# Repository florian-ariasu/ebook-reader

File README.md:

# OpenBook E-Reader

A portable, open-source e-book reader built around the **ESP32-C6** microcontroller, featuring an energy-efficient E-Paper display, microSD storage, environmental sensing, and a comprehensive power management system.

---

## System Architecture

### Block Diagram

The architecture focuses on a high-efficiency 3.3V power rail and shared communication buses (SPI/I2C):

- **ESP32-C6** – Main MCU managing UI, file systems, and wireless connectivity.
- **E-Paper Display** – 1.5" (200x200px) ultra-low-power screen.
- **Power Management** – Includes the **XC6220** 1A LDO for 3.3V regulation and **MCP73831** for Li-Po charging.
- **Battery Monitoring** – **MAX17048G+T10** fuel gauge for precision voltage and SoC tracking.
- **RTC (DS3231SN)** – Real-time clock with a **CPH3225A Supercapacitor** for power backup.
- **BME680 Sensor** – Integrated environmental sensing (Temp, Humidity, Pressure, Gas).
- **External Flash (64MB)** – Winbond **W25Q512** for extended storage and caching.

---

## Bill of Materials (BOM)

Access the full list of components used in this design, including technical specifications and sourcing links:

[Access the Bill of Materials (CSV)](Manufacturing/BOM.csv)

---

## Hardware Overview

### Power Supply & Charging

The system supports primary power via **USB-C** (5V). Charging is handled by the **MCP73831** controller. A high-performance **XC6220A331MR-G** LDO regulator converts the input/battery voltage to a stable **3.3V** to power the ESP32 and peripherals. Circuit protection includes a **USBLC6-2SC6Y** ESD protector and several **PGB1010** varistors.

### Storage Subsystems

- **MicroSD Card (J4)**: SPI-based interface for external library storage
- **NOR Flash (U1)**: 512Mb (64MB) SPI flash memory for firmware extensions

---

## ESP32-C6 Pin Allocation

| Function           | ESP32-C6 Pins        | Notes                       |
|--------------------|----------------------|-----------------------------|
| MicroSD Card       | IO2, IO3, IO4, IO5   | SPI                         |
| E-Paper Display    | IO8, IO9, IO10       | SPI                         |
| Shared I2C Bus     | IO6 (SCL), IO7 (SDA) | BME680, RTC, and Fuel Gauge |
| External Flash     | IO0, IO1, IO2        | SPI (Shared Bus)            |
| Reset Button       | IO9                  | Reset functionality         |
| UI Button (Change) | IO10                 | Navigation/Mode control     |
| UART Debug         | IO20 (TX), IO21 (RX) | Serial communication        |

---

## Visual Assets

All design-related documentation is located in the `Images/` directory:

- [Schematic](Images/schematic.png)
- [PCB Top View](Images/pcb-top.png)
- [PCB Bottom View](Images/pcb-bottom.png)
- [3D Model](Images/3d-model-2.png)
- [OpenBook Enclosure](Images/3d-model-enclosure.png)

---

## Known Issues

- **SMD Hole Errors**: Two minor SMD hole warnings were manually approved during the PCB routing phase. These were verified as non-critical for the final manufacturing.

---

## Compliance & Design Constraints

- All SMD components are **0402** package size (unless specified).
- Optimized for single-side component placement (Top-layer).
- Implemented via stitching and dual-layer ground planes for thermal/EMC stability.
- RF Isolation: The ESP32 antenna area is kept clear of copper and traces.
- Passed all Design Rule Checks (DRC) and Electrical Rule Checks (ERC).

---

- Designed the full ESP32-C6 pinout across SPI and I²C buses, integrating the E-Paper display, BME680 sensor, RTC, fuel gauge, NOR flash, and microSD card on shared communication lines.
- Managed the PCB routing phase in Autodesk Fusion 360, resolving DRC and ERC violations and manually approving non-critical SMD hole warnings after physical verification.
- Implemented dual-layer ground planes with via stitching for thermal and EMC stability, and maintained RF isolation by keeping the ESP32 antenna area clear of copper and traces.

---

## Development Notes

This is a 3rd-year TSC course assignment, designed in Autodesk Fusion 360 using a student license.

---

## Licensing

This project is licensed under the **[GPL-3.0 license](LICENCE)**.

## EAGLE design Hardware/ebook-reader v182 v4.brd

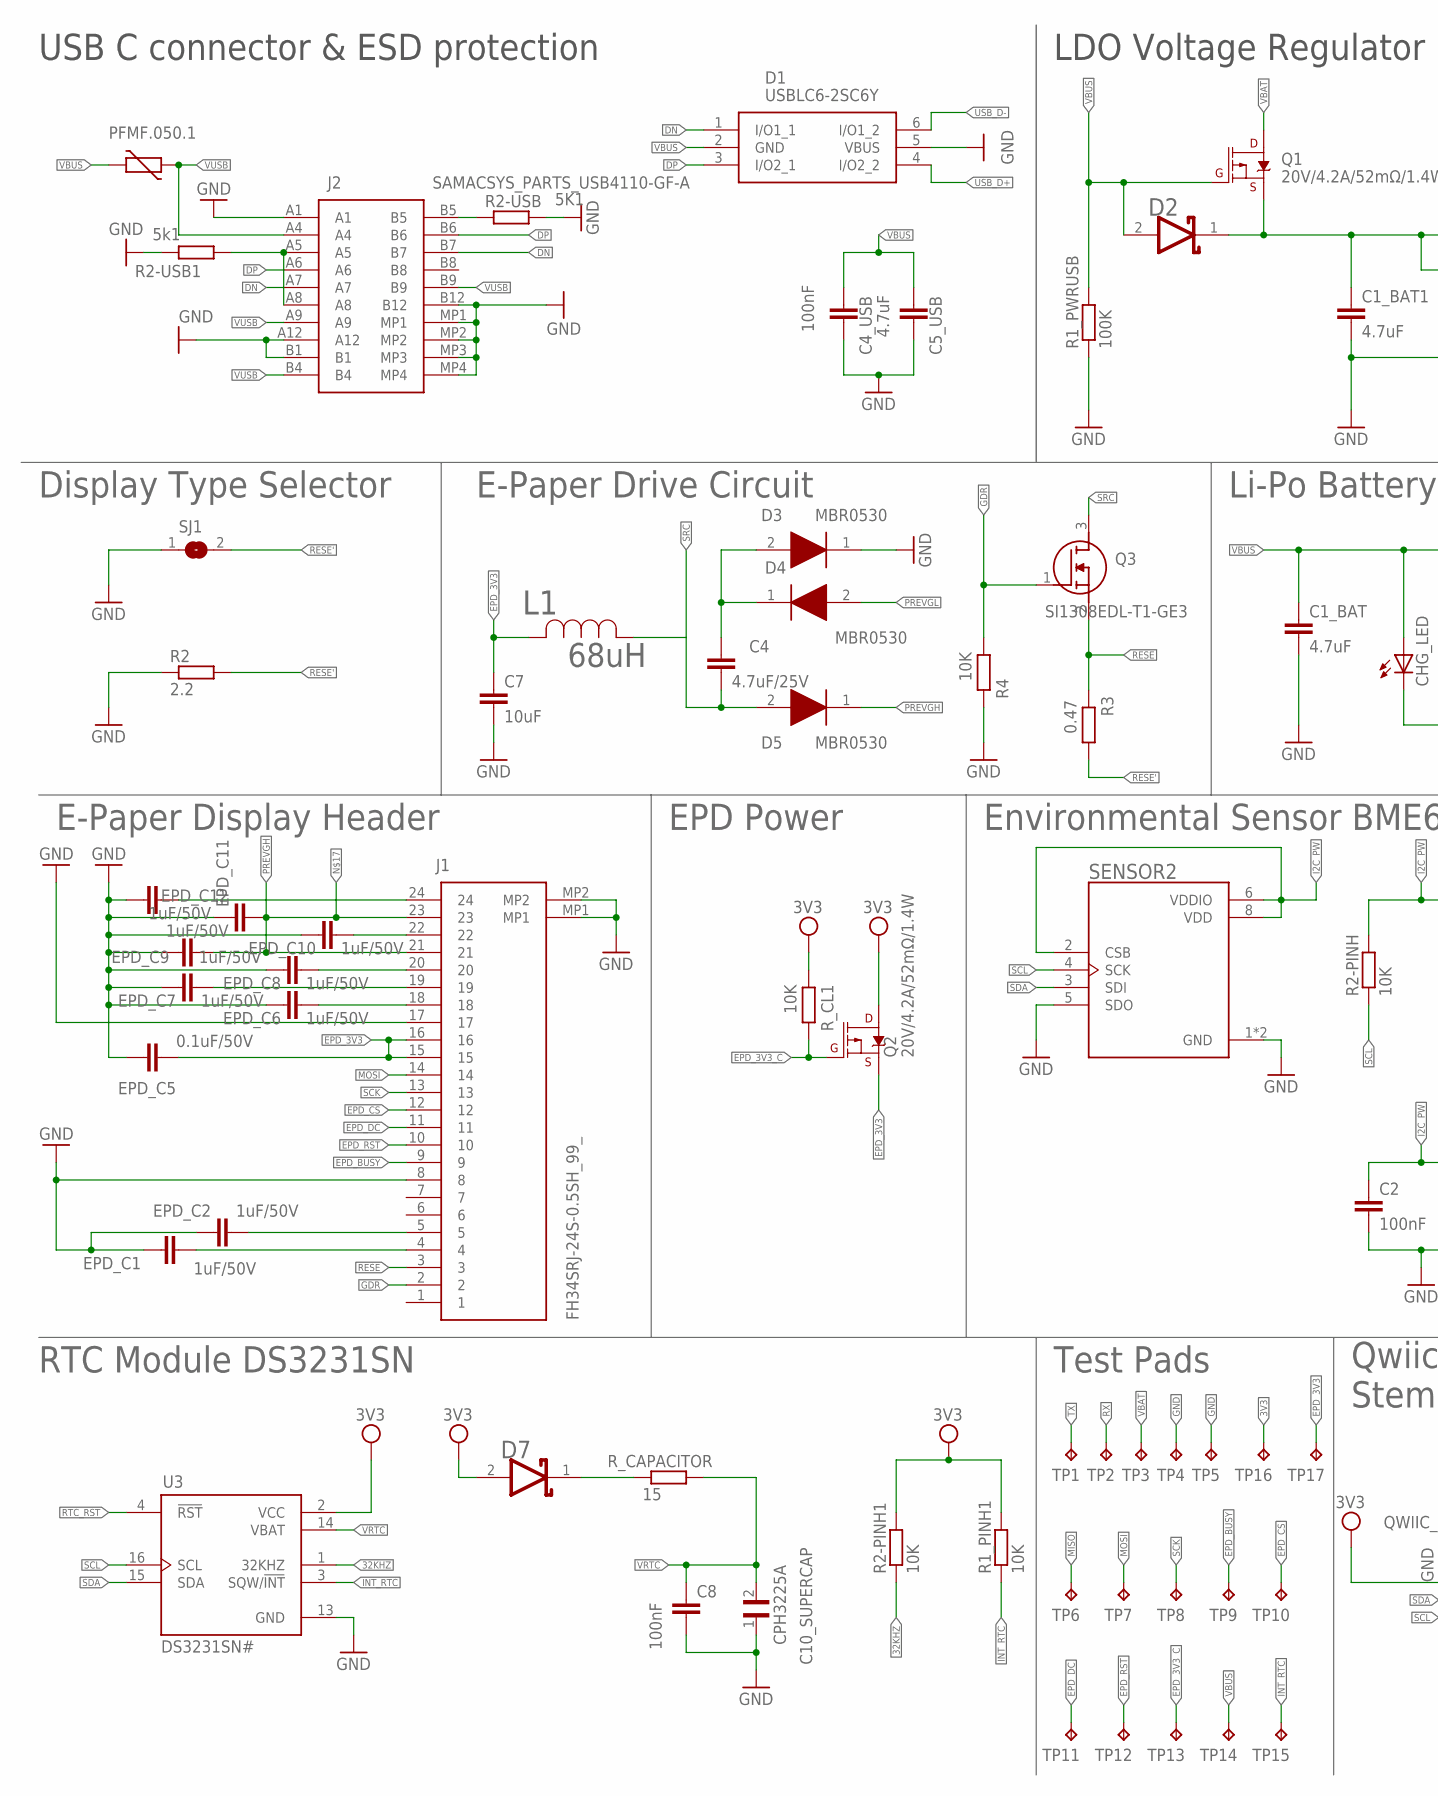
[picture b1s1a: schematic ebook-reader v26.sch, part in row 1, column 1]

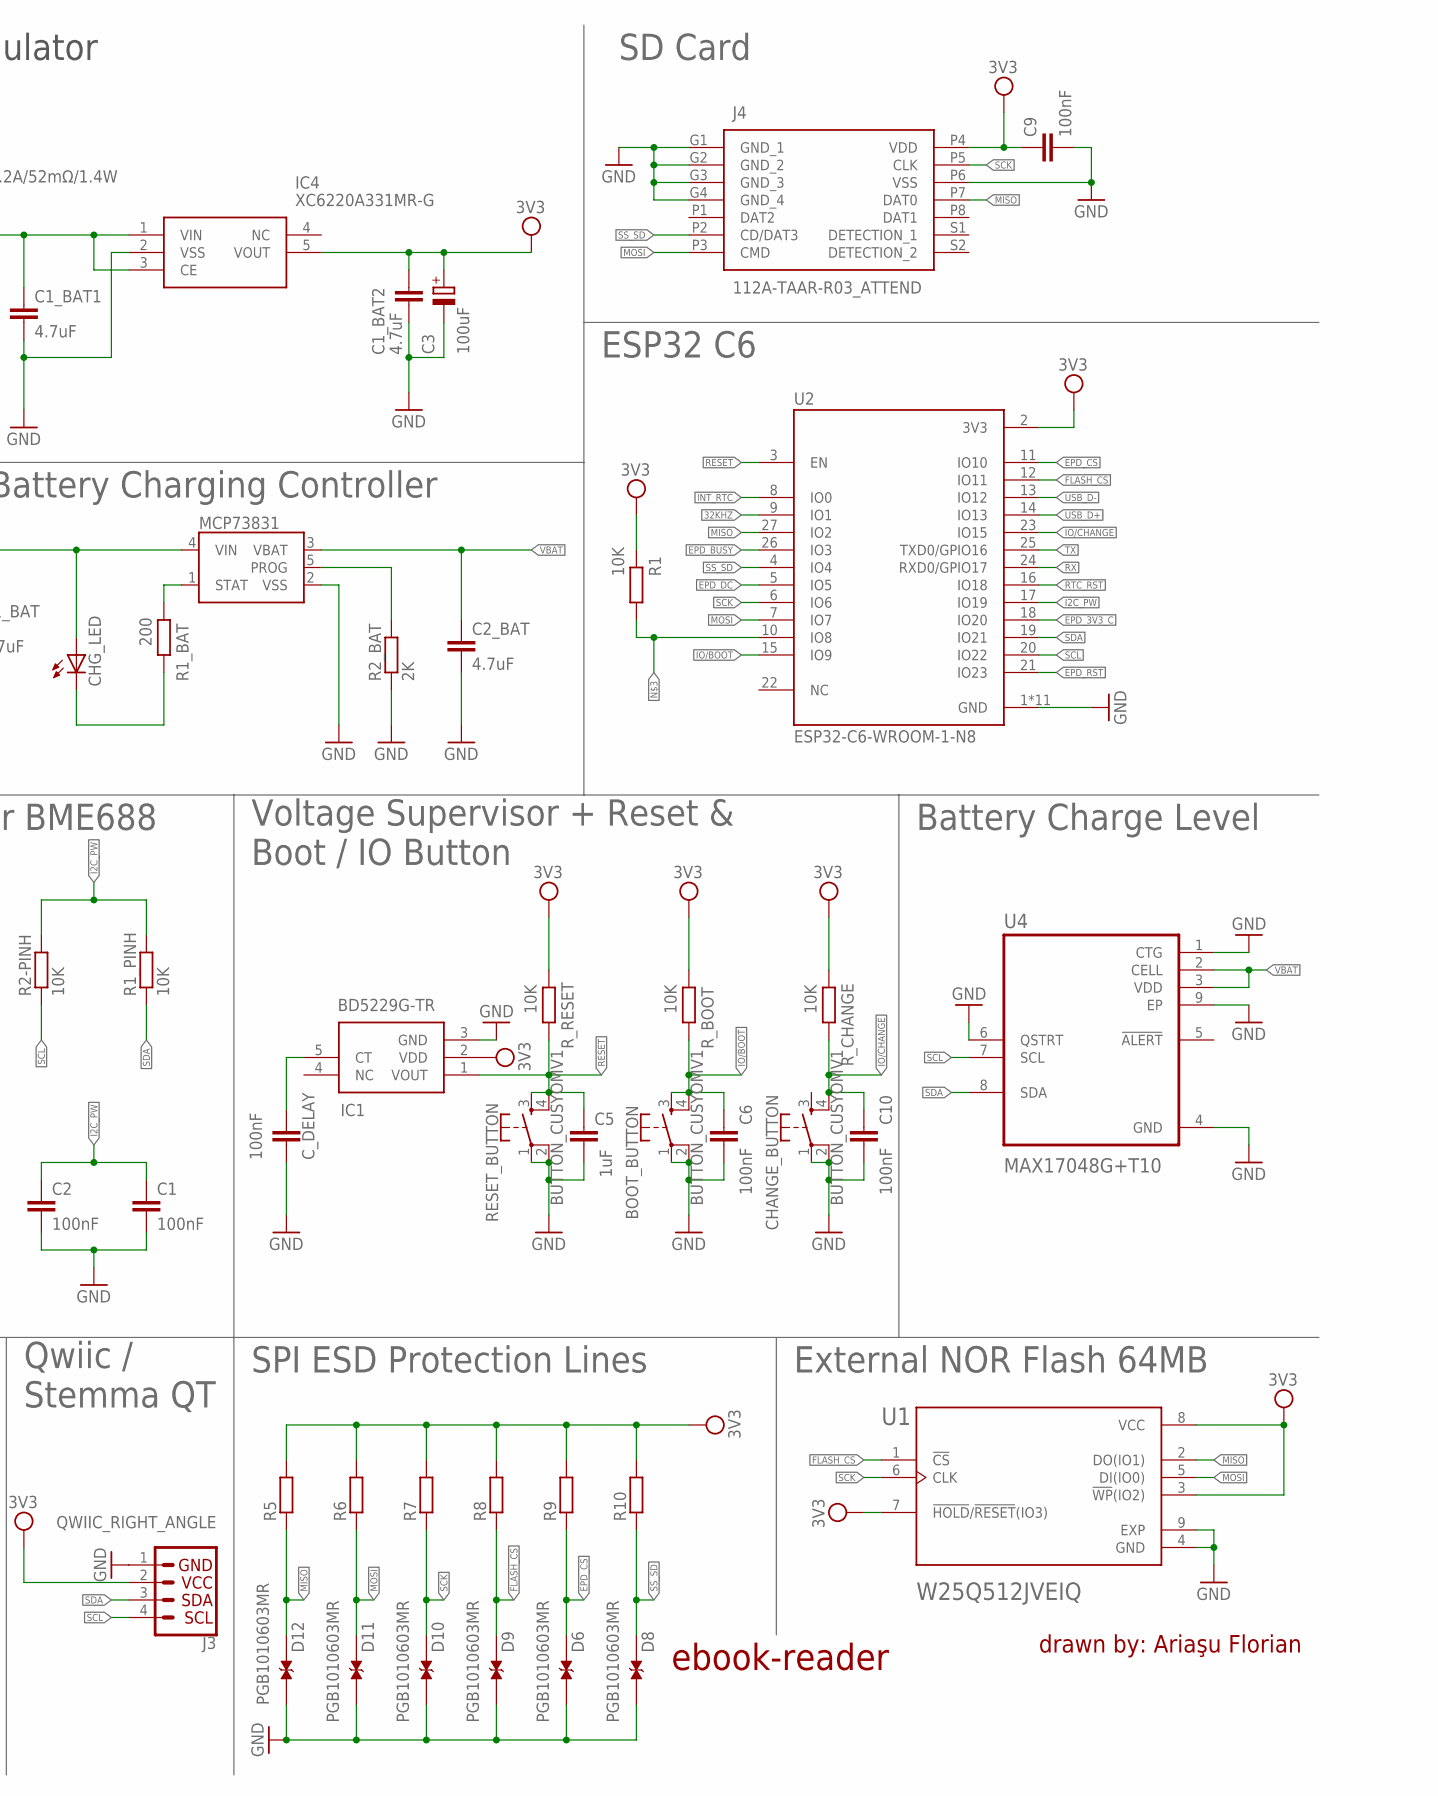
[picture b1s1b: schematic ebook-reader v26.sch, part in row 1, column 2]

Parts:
BOOT_BUTTON: BUTTON_CUSYOMV1; MYBUTTON
C1, C2, C4_USB, C6, C8, C9, C10: 100nF; EAGLE-LTSPICE_C0402
C1_BAT, C1_BAT1, C1_BAT2, C2_BAT, C5_USB: 4.7uF; EAGLE-LTSPICE_C0402
C3: 100uF; RCL_CT3528
C4: 4.7uF/25V; EAGLE-LTSPICE_C0402
C5: 1uF; EAGLE-LTSPICE_C0402
C7: 10uF; EAGLE-LTSPICE_C0402
C10_SUPERCAP: CPH3225A; CAPCP3225X100N
CHANGE_BUTTON: BUTTON_CUSYOMV1; MYBUTTON
CHG_LED: ADAFRUIT_LEDCHIP-LED0603; ADAFRUIT_CHIP-LED0603
C_DELAY: 100nF; EAGLE-LTSPICE_C0402
D1: USBLC6-2SC6Y; SOT95P280X145-6N
D2, D7: ESP32_WROVER_AVX---SD0805S020S1R0_AVX_SD0805S020S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; ESP32_WROVER_AVX---SD0805S020S1R0_AVX_SD0805S020S1R0_0
D3, D4, D5: MBR0530; SOD3716X135N
D6, D8, D9, D10, D11, D12: PGB1010603MR; DIOC1608X36N
EPD_C1, EPD_C2, EPD_C6, EPD_C7, EPD_C8, EPD_C9, EPD_C10, EPD_C11, EPD_C12: 1uF/50V; EAGLE-LTSPICE_C0402
EPD_C5: 0.1uF/50V; EAGLE-LTSPICE_C0402
IC1: BD5229G-TR; SOT95P280X125-5N
IC4: XC6220A331MR-G; SOT95P280X120-5N
J1: FH34SRJ-24S-0.5SH_99_; FH34SRJ24S05SH99
J2: SAMACSYS_PARTS_USB4110-GF-A; SAMACSYS_PARTS_USB4110GFA
J3: QWIIC_RIGHT_ANGLE; JST04_1MM_RA
J4: 112A-TAAR-R03_ATTEND; 112ATAARR03ATTEND
L1: 68uH; IND_4828-WE-TPC_WRE
MCP73831: ESP32_WROVER_SPARKFUN-IC-POWER_MCP73831; ESP32_WROVER_SPARKFUN-IC-POWER_SOT23-5
PFMF.050.1: ESP32C6_VARISTORCN1812; ESP32C6_VARISTOR_CT/CN1812
Q1, Q2: 20V/4.2A/52mΩ/1.4W; ESP32_WROVER_SPARKFUN-DISCRETESEMI_SOT23-3
Q3: SI1308EDL-T1-GE3; SOT65P210X110-3N
R1, R1_PINH, R1_PINH1, R2-PINH, R2-PINH1, R4: 10K; ESP32_WROVER_EAGLE-LTSPICE_R0402
R1_BAT: 200; ESP32_WROVER_EAGLE-LTSPICE_R0402
R1_PWRUSB: 100K; ESP32_WROVER_EAGLE-LTSPICE_R0402
R2: 2.2; ESP32_WROVER_EAGLE-LTSPICE_R0402
R2-USB: 5K1; ESP32_WROVER_EAGLE-LTSPICE_R0402
R2-USB1: 5k1; ESP32_WROVER_EAGLE-LTSPICE_R0402
R2_BAT: 2K; ESP32_WROVER_EAGLE-LTSPICE_R0402
R3: 0.47; ESP32_WROVER_EAGLE-LTSPICE_R0402
R5, R6, R7, R8, R9, R10: ESP32_WROVER_EAGLE-LTSPICE_RR0402; ESP32_WROVER_EAGLE-LTSPICE_R0402
RESET_BUTTON: BUTTON_CUSYOMV1; MYBUTTON
R_BOOT: 10K; ESP32_WROVER_EAGLE-LTSPICE_R0402
R_CAPACITOR: 15; ESP32_WROVER_EAGLE-LTSPICE_R0402
R_CHANGE: 10K; ESP32_WROVER_EAGLE-LTSPICE_R0402
R_CL1: 10K; ESP32_WROVER_EAGLE-LTSPICE_R0402
R_RESET: 10K; ESP32_WROVER_EAGLE-LTSPICE_R0402
SENSOR2: ESP32_WROVER_BME680_BME680; ESP32_WROVER_BME680_PSON80P300X300X100-8N
SJ1: SJ
TP1, TP2, TP3, TP4, TP5, TP6, TP7, TP8, TP9, TP10, TP11, TP12, TP13, TP14, TP15, TP16, TP17: TPTP20R; TP20R
U1: W25Q512JVEIQ; SON127P600X800X80-9N
U2: ESP32-C6-WROOM-1-N8; XCVR_ESP32-C6-WROOM-1-N8
U3: DS3231SN#; SOIC127P1032X265-16N
U4: MAX17048G+T10; SON50P200X200X80-9N

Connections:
3V3: C1_BAT2.1, C3.+, C9.1, D7.2 (ANODE), IC1.2 (VDD), IC4.5 (VOUT), J3.2, J4.P4 (VDD), Q2.3 (D), R1.2, R1_PINH1.2, R2-PINH1.2, R5.2, R6.2, R7.2, R8.2, R9.2, R10.2, R_BOOT.2, R_CHANGE.2, R_CL1.2, R_RESET.2, TP16.TP, U1.3 (!WP!(IO2)), U1.7 (!HOLD!/!RESET!(IO3)), U1.8 (VCC), U2.2 (3V3), U3.2 (VCC)
32KHZ: R2-PINH1.1, U2.9 (IO1), U3.1 (32KHZ)
DN: D1.1 (I/O1_1), J2.A7, J2.B7
DP: D1.3 (I/O2_1), J2.A6, J2.B6
EPD_3V3: C7.1, EPD_C5.2, J1.15, J1.16, L1.2, Q2.2 (S), TP17.TP
EPD_3V3_C: Q2.1 (G), R_CL1.1, TP13.TP, U2.18 (IO20)
EPD_BUSY: J1.9, TP9.TP, U2.26 (IO3)
EPD_CS: D11.2, J1.12, R9.1, TP10.TP, U2.11 (IO10)
EPD_DC: J1.11, TP11.TP, U2.5 (IO5)
EPD_RST: J1.10, TP12.TP, U2.21 (IO23)
FLASH_CS: D10.2, R8.1, U1.1 (!CS), U2.12 (IO11)
GDR: J1.2, Q3.1 (G), R4.2
I2C_PW: C1.1, C2.1, R1_PINH.2, R2-PINH.2, SENSOR2.2 (CSB), SENSOR2.6 (VDDIO), SENSOR2.8 (VDD), U2.17 (IO19)
INT_RTC: R1_PINH1.1, TP15.TP, U2.8 (IO0), U3.3 (SQW/!INT)
IO/BOOT: BOOT_BUTTON.3, BOOT_BUTTON.4, C6.1, R_BOOT.1, U2.15 (IO9)
IO/CHANGE: C10.1, CHANGE_BUTTON.4, R_CHANGE.1, U2.23 (IO15)
MISO: D6.2, J4.P7 (DAT0), R5.1, TP6.TP, U1.2 (DO(IO1)), U2.27 (IO2)
MOSI: D9.2, J1.14, J4.P3 (CMD), R6.1, TP7.TP, U1.5 (DI(IO0)), U2.7 (IO7)
unnamed: J2.A5, J2.A8, R2-USB1.2
unnamed: J2.B5, R2-USB.1
unnamed: C1_BAT1.1, D2.1 (CATHODE), IC4.1 (VIN), IC4.3 (CE), Q1.2 (S)
unnamed: CHG_LED.C, R1_BAT.1
unnamed: C4.1, D3.2 (A), D4.1 (K)
unnamed: MCP73831.1 (STAT), R1_BAT.2
unnamed: MCP73831.5 (PROG), R2_BAT.2
unnamed: EPD_C1.2, J1.4
unnamed: EPD_C2.2, J1.5
unnamed: C_DELAY.1, IC1.5 (CT)
unnamed: D7.1 (CATHODE), R_CAPACITOR.1
unnamed: EPD_C12.2, J1.24
unnamed: EPD_C10.2, J1.22
unnamed: EPD_C8.2, J1.20
unnamed: EPD_C7.2, J1.19
unnamed: EPD_C6.2, J1.18
PREVGH: D5.1 (K)
RESE: J1.3, Q3.2 (S), R3.2
RESE': R2.2, R3.1, SJ1.2
RESET: C5.1, IC1.1 (VOUT), RESET_BUTTON.3, RESET_BUTTON.4, R_RESET.1, U2.3 (EN)
RTC_RST: U2.16 (IO18), U3.4 (!RST)
RX: TP2.TP, U2.24 (RXD0/GPIO17)
SCK: D8.2, J1.13, J4.P5 (CLK), R7.1, TP8.TP, U1.6 (CLK), U2.6 (IO6)
SCL: J3.4, R2-PINH.1, SENSOR2.4 (SCK), U2.20 (IO22), U3.16 (SCL), U4.7 (SCL)
SDA: J3.3, R1_PINH.1, SENSOR2.3 (SDI), U2.19 (IO21), U3.15 (SDA), U4.8 (SDA)
SRC: C4.2, D5.2 (A), L1.1, Q3.3 (D)
SS_SD: D12.2, J4.P2 (CD/DAT3), R10.1, U2.4 (IO4)
TX: TP1.TP, U2.25 (TXD0/GPIO16)
USB_D+: D1.4 (I/O2_2), U2.14 (IO13)
USB_D-: D1.6 (I/O1_2), U2.13 (IO12)
VBAT: C2_BAT.1, D2.2 (ANODE), MCP73831.3 (VBAT), Q1.1 (G), R1_PWRUSB.2, TP3.TP, U4.2 (CELL), U4.3 (VDD)
VBUS: C1_BAT.1, C4_USB.1, C5_USB.1, CHG_LED.A, D1.2 (GND), MCP73831.4 (VIN), PFMF.050.1.2, TP14.TP
VRTC: C8.1, C10_SUPERCAP.2, R_CAPACITOR.2, U3.14 (VBAT)
VUSB: J2.A4, J2.A9, J2.B4, J2.B9, PFMF.050.1.1

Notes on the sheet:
USB C connector & ESD protection
LDO Voltage Regulator
SD Card
Display Type Selector
E-Paper Drive Circuit
Li-Po Battery Charging Controller
ESP32 C6
E-Paper Display Header
EPD Power
Environmental Sensor BME688
Voltage Supervisor + Reset & Boot / IO Button
Battery Charge Level
RTC Module DS3231SN
Test Pads
Qwiic / Stemma QT
SPI ESD Protection Lines
External NOR Flash 64MB
ebook-reader
drawn by: Ariaşu Florian

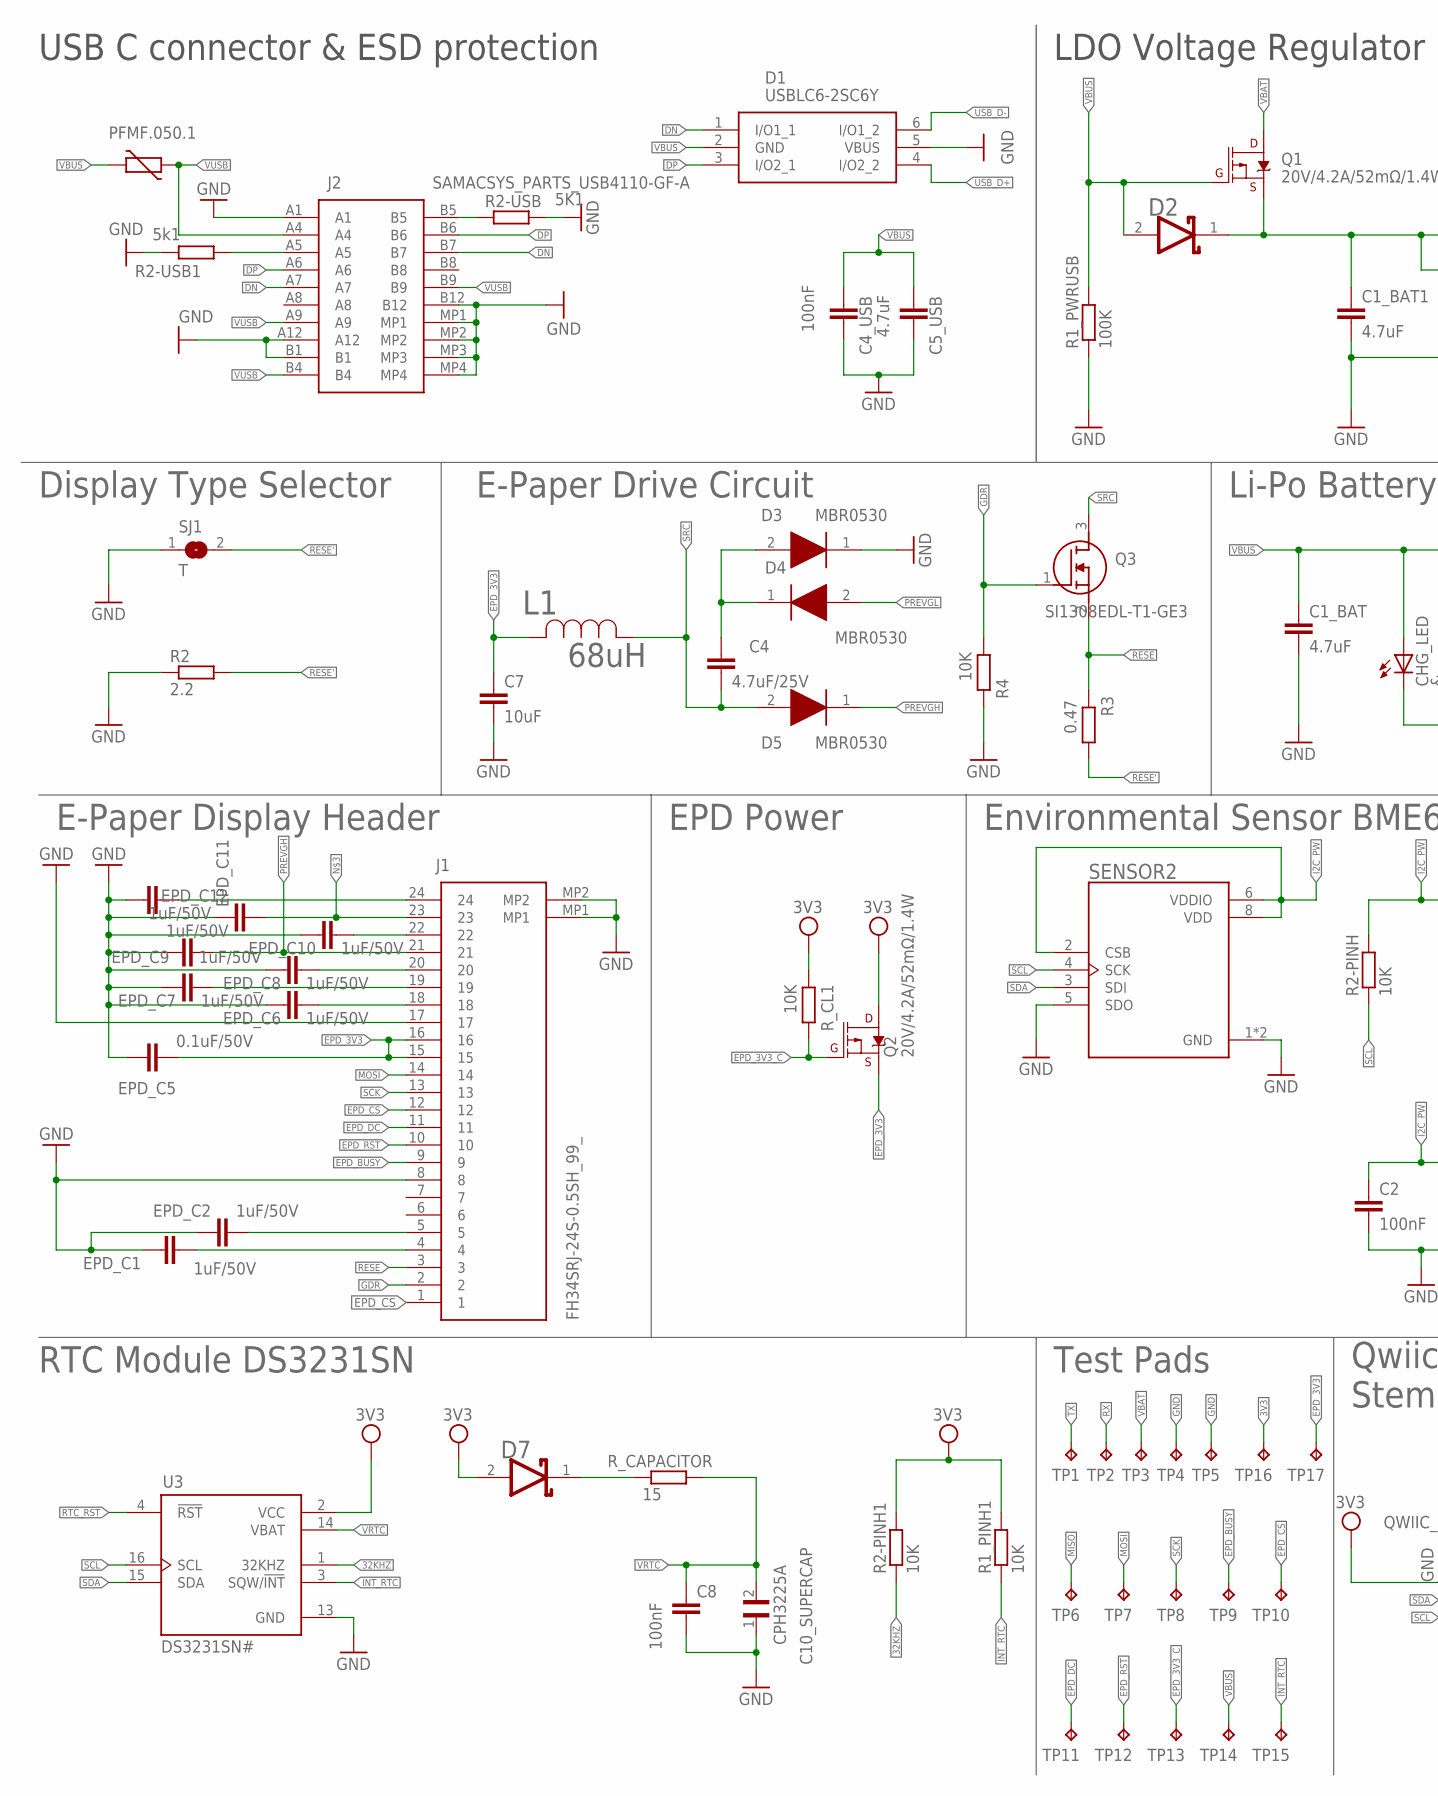
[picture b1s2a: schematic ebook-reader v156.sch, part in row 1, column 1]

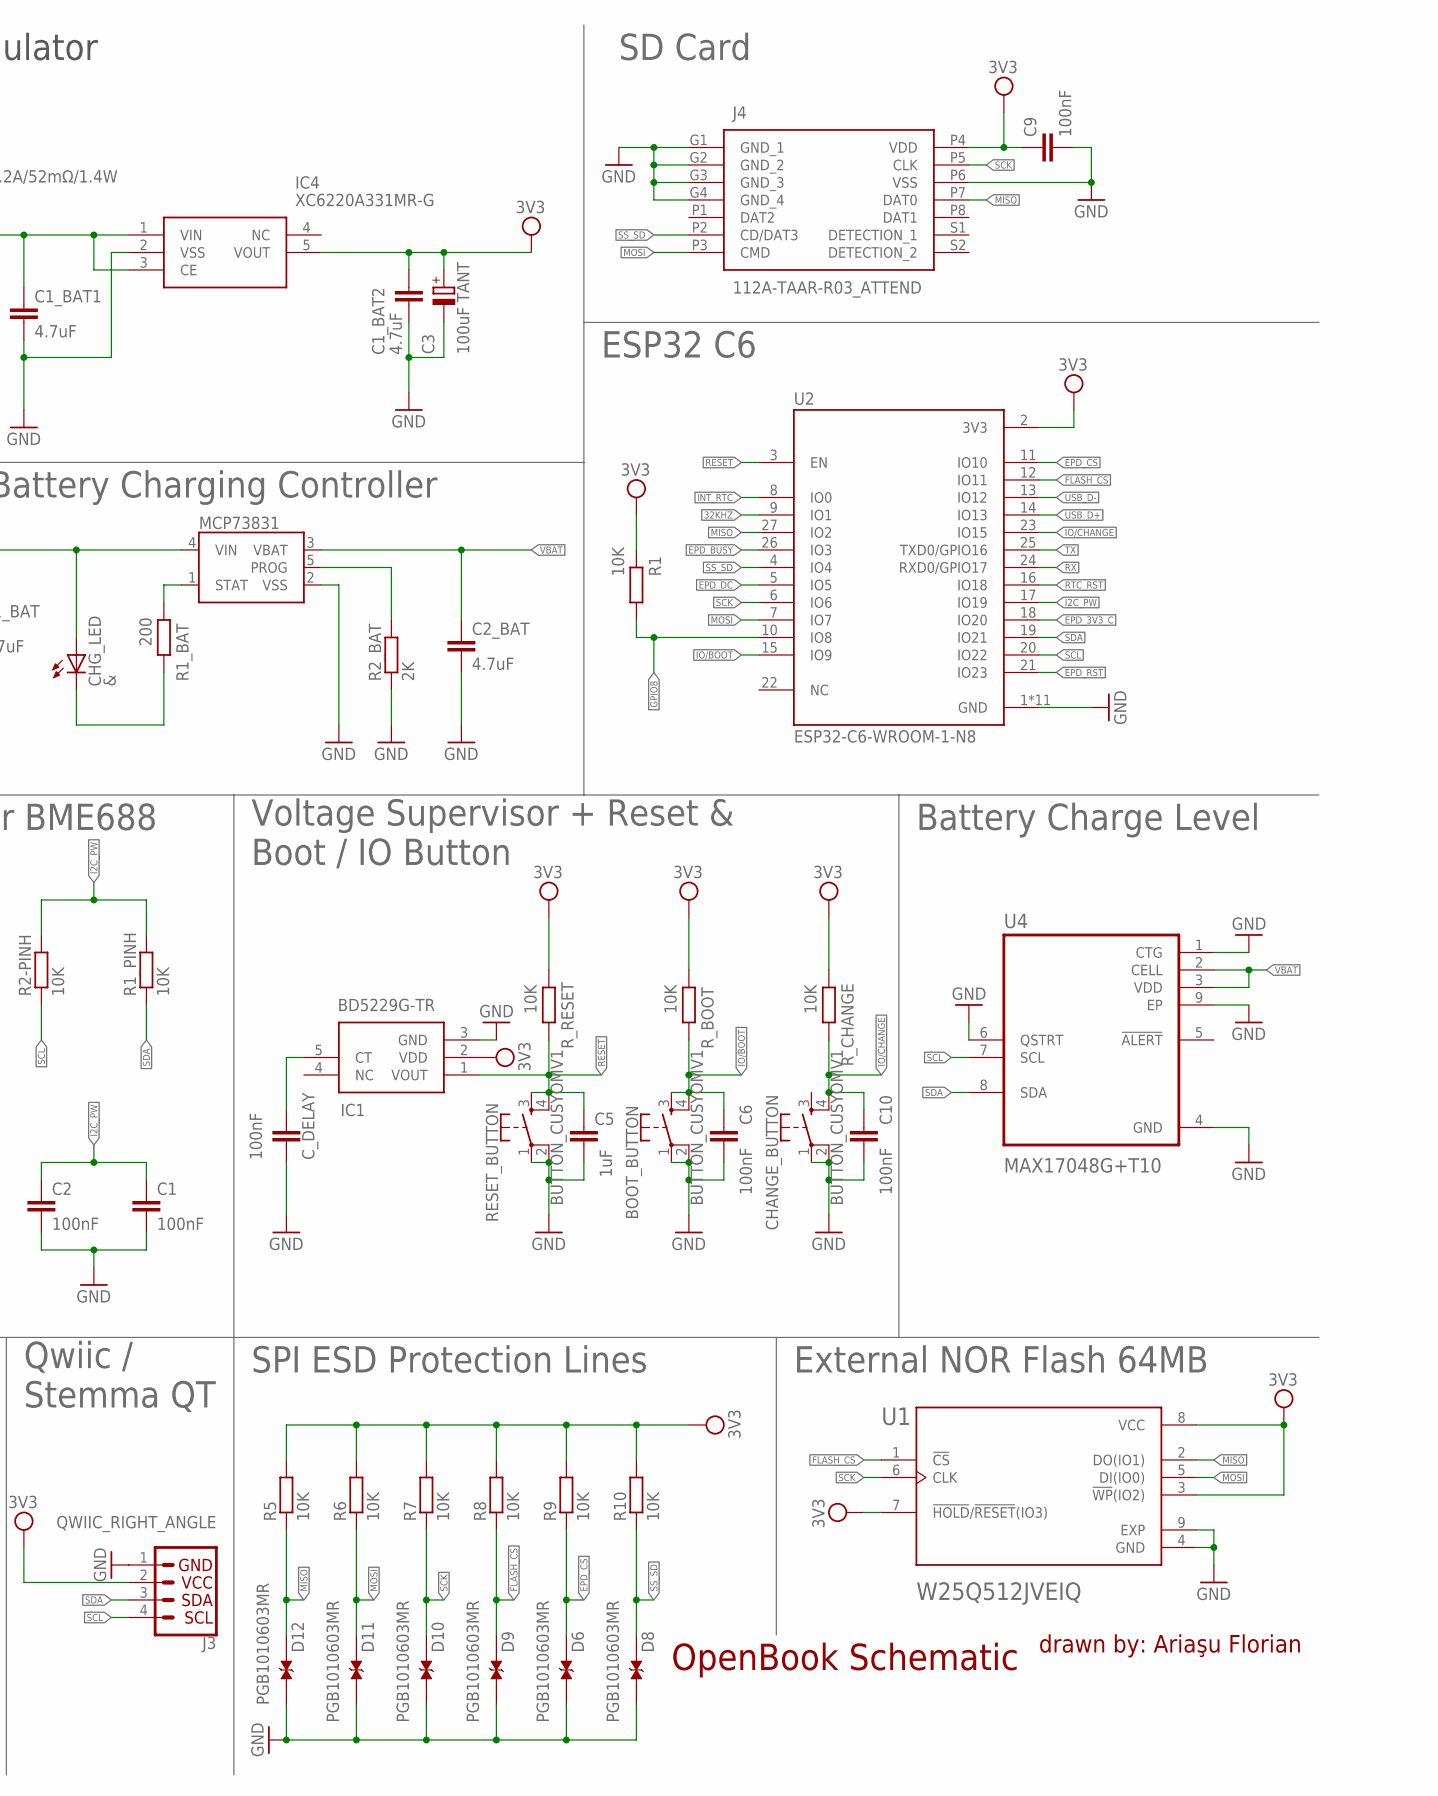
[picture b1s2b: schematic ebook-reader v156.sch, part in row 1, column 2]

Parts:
BOOT_BUTTON: BUTTON_CUSYOMV1; MYBUTTON
C1, C2, C4_USB, C6, C8, C9, C10: 100nF; EAGLE-LTSPICE_C0402
C1_BAT, C1_BAT1, C1_BAT2, C2_BAT, C5_USB: 4.7uF; EAGLE-LTSPICE_C0402
C3: 100uF TANT; RCL_CT3528
C4: 4.7uF/25V; EAGLE-LTSPICE_C0402
C5: 1uF; EAGLE-LTSPICE_C0402
C7: 10uF; EAGLE-LTSPICE_C0402
C10_SUPERCAP: CPH3225A; CAPCP3225X100N
CHANGE_BUTTON: BUTTON_CUSYOMV1; MYBUTTON
CHG_LED: &; ADAFRUIT_CHIP-LED0603
C_DELAY: 100nF; EAGLE-LTSPICE_C0402
D1: USBLC6-2SC6Y; SOT95P280X145-6N
D2, D7: ESP32_WROVER_AVX---SD0805S020S1R0_AVX_SD0805S020S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; ESP32_WROVER_AVX---SD0805S020S1R0_AVX_SD0805S020S1R0_0
D3, D4, D5: MBR0530; SOD3716X135N
D6, D8, D9, D10, D11, D12: PGB1010603MR; DIOC1608X36N
EPD_C1, EPD_C2, EPD_C6, EPD_C7, EPD_C8, EPD_C9, EPD_C10, EPD_C11, EPD_C12: 1uF/50V; EAGLE-LTSPICE_C0402
EPD_C5: 0.1uF/50V; EAGLE-LTSPICE_C0402
IC1: BD5229G-TR; SOT95P280X125-5N
IC4: XC6220A331MR-G; SOT95P280X120-5N
J1: FH34SRJ-24S-0.5SH_99_; FH34SRJ24S05SH99
J2: SAMACSYS_PARTS_USB4110-GF-A; SAMACSYS_PARTS_USB4110GFA
J3: QWIIC_RIGHT_ANGLE; JST04_1MM_RA
J4: 112A-TAAR-R03_ATTEND; 112ATAARR03ATTEND
L1: 68uH; IND_4828-WE-TPC_WRE
MCP73831: ESP32_WROVER_SPARKFUN-IC-POWER_MCP73831; ESP32_WROVER_SPARKFUN-IC-POWER_SOT23-5
PFMF.050.1: ESP32C6_VARISTORCN1812; ESP32C6_VARISTOR_CT/CN1812
Q1, Q2: 20V/4.2A/52mΩ/1.4W; ESP32_WROVER_SPARKFUN-DISCRETESEMI_SOT23-3
Q3: SI1308EDL-T1-GE3; SOT65P210X110-3N
R1, R1_PINH, R1_PINH1, R2-PINH, R2-PINH1, R4, R5, R6, R7, R8, R9, R10: 10K; ESP32_WROVER_EAGLE-LTSPICE_R0402
R1_BAT: 200; ESP32_WROVER_EAGLE-LTSPICE_R0402
R1_PWRUSB: 100K; ESP32_WROVER_EAGLE-LTSPICE_R0402
R2: 2.2; ESP32_WROVER_EAGLE-LTSPICE_R0402
R2-USB: 5K1; ESP32_WROVER_EAGLE-LTSPICE_R0402
R2-USB1: 5k1; ESP32_WROVER_EAGLE-LTSPICE_R0402
R2_BAT: 2K; ESP32_WROVER_EAGLE-LTSPICE_R0402
R3: 0.47; ESP32_WROVER_EAGLE-LTSPICE_R0402
RESET_BUTTON: BUTTON_CUSYOMV1; MYBUTTON
R_BOOT: 10K; ESP32_WROVER_EAGLE-LTSPICE_R0402
R_CAPACITOR: 15; ESP32_WROVER_EAGLE-LTSPICE_R0402
R_CHANGE: 10K; ESP32_WROVER_EAGLE-LTSPICE_R0402
R_CL1: 10K; ESP32_WROVER_EAGLE-LTSPICE_R0402
R_RESET: 10K; ESP32_WROVER_EAGLE-LTSPICE_R0402
SENSOR2: ESP32_WROVER_BME680_BME680; ESP32_WROVER_BME680_PSON80P300X300X100-8N
SJ1: T; SJ
TP1, TP2, TP3, TP4, TP5, TP6, TP7, TP8, TP9, TP10, TP11, TP12, TP13, TP14, TP15, TP16, TP17: TPTP20R; TP20R
U1: W25Q512JVEIQ; SON127P600X800X80-9N
U2: ESP32-C6-WROOM-1-N8; XCVR_ESP32-C6-WROOM-1-N8
U3: DS3231SN#; SOIC127P1032X265-16N
U4: MAX17048G+T10; SON50P200X200X80-9N

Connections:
3V3: C1_BAT2.1, C3.+, C9.1, D7.2 (ANODE), IC1.2 (VDD), IC4.5 (VOUT), J3.2, J4.P4 (VDD), Q2.3 (D), R1.2, R1_PINH1.2, R2-PINH1.2, R5.2, R6.2, R7.2, R8.2, R9.2, R10.2, R_BOOT.2, R_CHANGE.2, R_CL1.2, R_RESET.2, TP16.TP, U1.3 (!WP!(IO2)), U1.7 (!HOLD!/!RESET!(IO3)), U1.8 (VCC), U2.2 (3V3), U3.2 (VCC)
32KHZ: R2-PINH1.1, U2.9 (IO1), U3.1 (32KHZ)
DN: D1.1 (I/O1_1), J2.A7, J2.B7
DP: D1.3 (I/O2_1), J2.A6, J2.B6
EPD_3V3: C7.1, EPD_C5.2, J1.15, J1.16, L1.2, Q2.2 (S), TP17.TP
EPD_3V3_C: Q2.1 (G), R_CL1.1, TP13.TP, U2.18 (IO20)
EPD_BUSY: J1.9, TP9.TP, U2.26 (IO3)
EPD_CS: D11.2, J1.12, R9.1, TP10.TP, U2.11 (IO10)
EPD_DC: J1.11, TP11.TP, U2.5 (IO5)
EPD_RST: J1.10, TP12.TP, U2.21 (IO23)
FLASH_CS: D10.2, R8.1, U1.1 (!CS), U2.12 (IO11)
GDR: J1.2, Q3.1 (G), R4.2
I2C_PW: C1.1, C2.1, R1_PINH.2, R2-PINH.2, SENSOR2.2 (CSB), SENSOR2.6 (VDDIO), SENSOR2.8 (VDD), U2.17 (IO19)
INT_RTC: R1_PINH1.1, TP15.TP, U2.8 (IO0), U3.3 (SQW/!INT)
IO/BOOT: BOOT_BUTTON.3, BOOT_BUTTON.4, C6.1, R_BOOT.1, U2.15 (IO9)
IO/CHANGE: C10.1, CHANGE_BUTTON.4, R_CHANGE.1, U2.23 (IO15)
MISO: D6.2, J4.P7 (DAT0), R5.1, TP6.TP, U1.2 (DO(IO1)), U2.27 (IO2)
MOSI: D9.2, J1.14, J4.P3 (CMD), R6.1, TP7.TP, U1.5 (DI(IO0)), U2.7 (IO7)
unnamed 18: J2.A5, R2-USB1.2; also elsewhere on the board
unnamed: J2.B5, R2-USB.1
unnamed: C1_BAT1.1, D2.1 (CATHODE), IC4.1 (VIN), IC4.3 (CE), Q1.2 (S)
unnamed: CHG_LED.C, R1_BAT.1
unnamed: C4.1, D3.2 (A), D4.1 (K)
unnamed: MCP73831.1 (STAT), R1_BAT.2
unnamed: MCP73831.5 (PROG), R2_BAT.2
unnamed: EPD_C1.2, J1.4
unnamed: EPD_C2.2, J1.5
unnamed: C_DELAY.1, IC1.5 (CT)
unnamed: D7.1 (CATHODE), R_CAPACITOR.1
unnamed: EPD_C12.2, J1.24
unnamed: EPD_C10.2, J1.22
unnamed: EPD_C8.2, J1.20
unnamed: EPD_C7.2, J1.19
unnamed: EPD_C6.2, J1.18
PREVGH: D5.1 (K)
RESE: J1.3, Q3.2 (S), R3.2
RESE': R2.2, R3.1, SJ1.2
RESET: C5.1, IC1.1 (VOUT), RESET_BUTTON.3, RESET_BUTTON.4, R_RESET.1, U2.3 (EN)
RTC_RST: U2.16 (IO18), U3.4 (!RST)
RX: TP2.TP, U2.24 (RXD0/GPIO17)
SCK: D8.2, J1.13, J4.P5 (CLK), R7.1, TP8.TP, U1.6 (CLK), U2.6 (IO6)
SCL: J3.4, R2-PINH.1, SENSOR2.4 (SCK), U2.20 (IO22), U3.16 (SCL), U4.7 (SCL)
SDA: J3.3, R1_PINH.1, SENSOR2.3 (SDI), U2.19 (IO21), U3.15 (SDA), U4.8 (SDA)
SRC: C4.2, D5.2 (A), L1.1, Q3.3 (D)
SS_SD: D12.2, J4.P2 (CD/DAT3), R10.1, U2.4 (IO4)
TX: TP1.TP, U2.25 (TXD0/GPIO16)
USB_D+: D1.4 (I/O2_2), U2.14 (IO13)
USB_D-: D1.6 (I/O1_2), U2.13 (IO12)
VBAT: C2_BAT.1, D2.2 (ANODE), MCP73831.3 (VBAT), Q1.1 (G), R1_PWRUSB.2, TP3.TP, U4.2 (CELL), U4.3 (VDD)
VBUS: C1_BAT.1, C4_USB.1, C5_USB.1, CHG_LED.A, D1.2 (GND), MCP73831.4 (VIN), PFMF.050.1.2, TP14.TP
VRTC: C8.1, C10_SUPERCAP.2, R_CAPACITOR.2, U3.14 (VBAT)
VUSB: J2.A4, J2.A9, J2.B4, J2.B9, PFMF.050.1.1

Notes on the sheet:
USB C connector & ESD protection
LDO Voltage Regulator
SD Card
Display Type Selector
E-Paper Drive Circuit
Li-Po Battery Charging Controller
ESP32 C6
E-Paper Display Header
EPD Power
Environmental Sensor BME688
Voltage Supervisor + Reset & Boot / IO Button
Battery Charge Level
RTC Module DS3231SN
Test Pads
Qwiic / Stemma QT
SPI ESD Protection Lines
External NOR Flash 64MB
OpenBook Schematic
drawn by: Ariaşu Florian

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
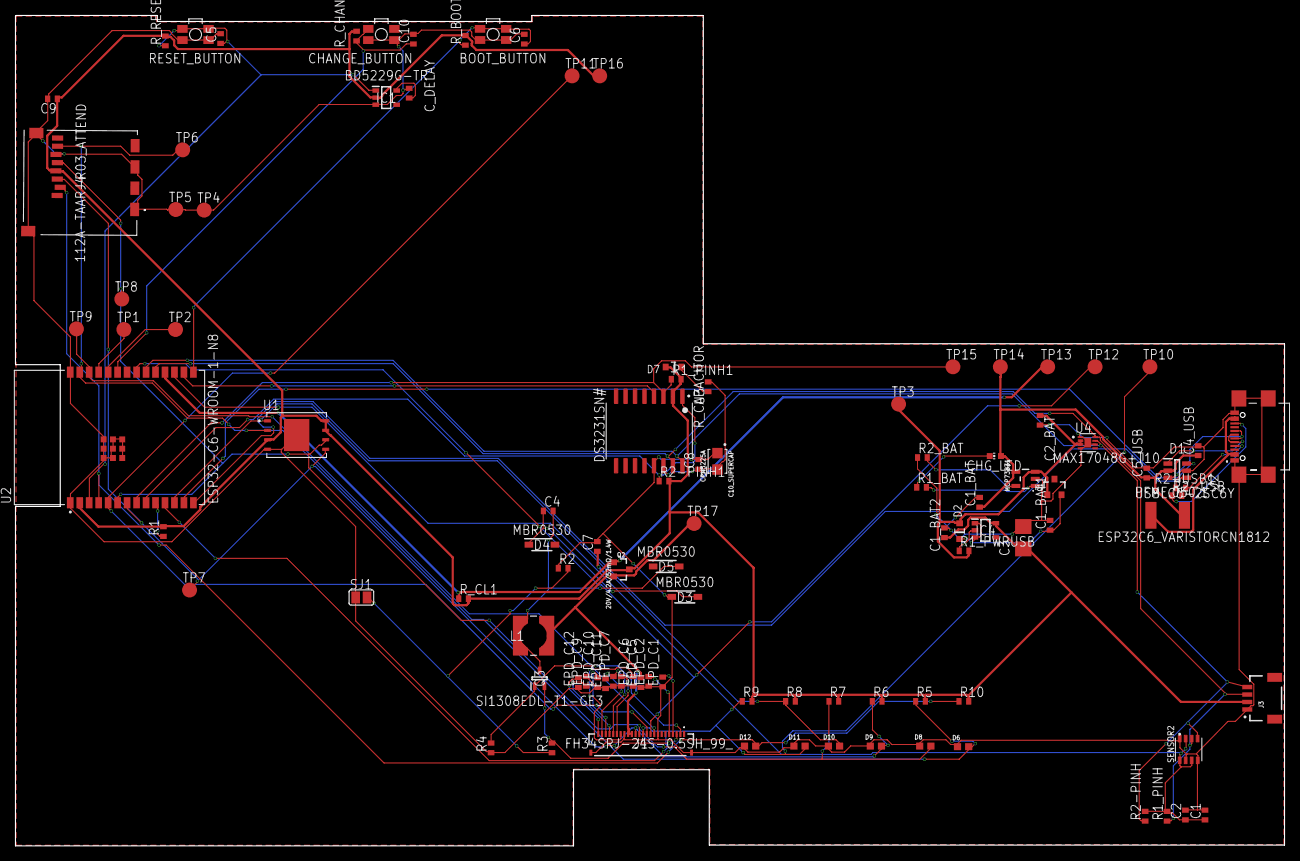
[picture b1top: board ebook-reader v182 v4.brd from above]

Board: 2 copper layers, 170.1 x 111.3 mm, 103 parts (0 on the bottom side), 55 nets.

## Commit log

2025-04-06 add project main directories
2025-04-06 add LICENCE
2025-04-06 rename LICENSE
2025-04-06 add the diagram
2025-04-06 add BOM file
2025-04-06 rename BOM file
2025-04-10 add final touches for 3d-model
2025-04-10 change file hierarchy
2025-04-10 rename some ./Images files
2025-04-10 add final .sch and .brd versions
2025-04-11 add final .sch and .brd final versions
2025-04-11 add 3d-model final version before enclosure
2025-04-11 add updated images
2025-04-12 add enclosure new version
2025-04-12 add .step file
2025-09-16 upload full project
2025-10-12 Revise README for clarity and project overview
    Updated README.md to clarify project details and structure.
2026-02-12 replaced diagram.png and added gitignore file
2026-02-12 Revise README for project overview and details
    Updated project description, system architecture, and compliance details in README.md.
2026-02-12 Update README.md for formatting and content clarity
2026-02-23 Revise README with project details and development notes
    Updated project description, added development notes, and refined system architecture details.
2026-03-03 Update README with project details and structure

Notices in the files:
parts and their libraries:
DeskAssistant v19 v1: COPYRIGHT: Copyright (C) 2024 Ultra Librarian. All rights reserved.
